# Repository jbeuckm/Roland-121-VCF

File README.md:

# Roland-121-VCF
Based on http://www.frequencycentral.co.uk/wp-content/uploads/2012/05/Roland-121-VCF-Build-Doc.pdf

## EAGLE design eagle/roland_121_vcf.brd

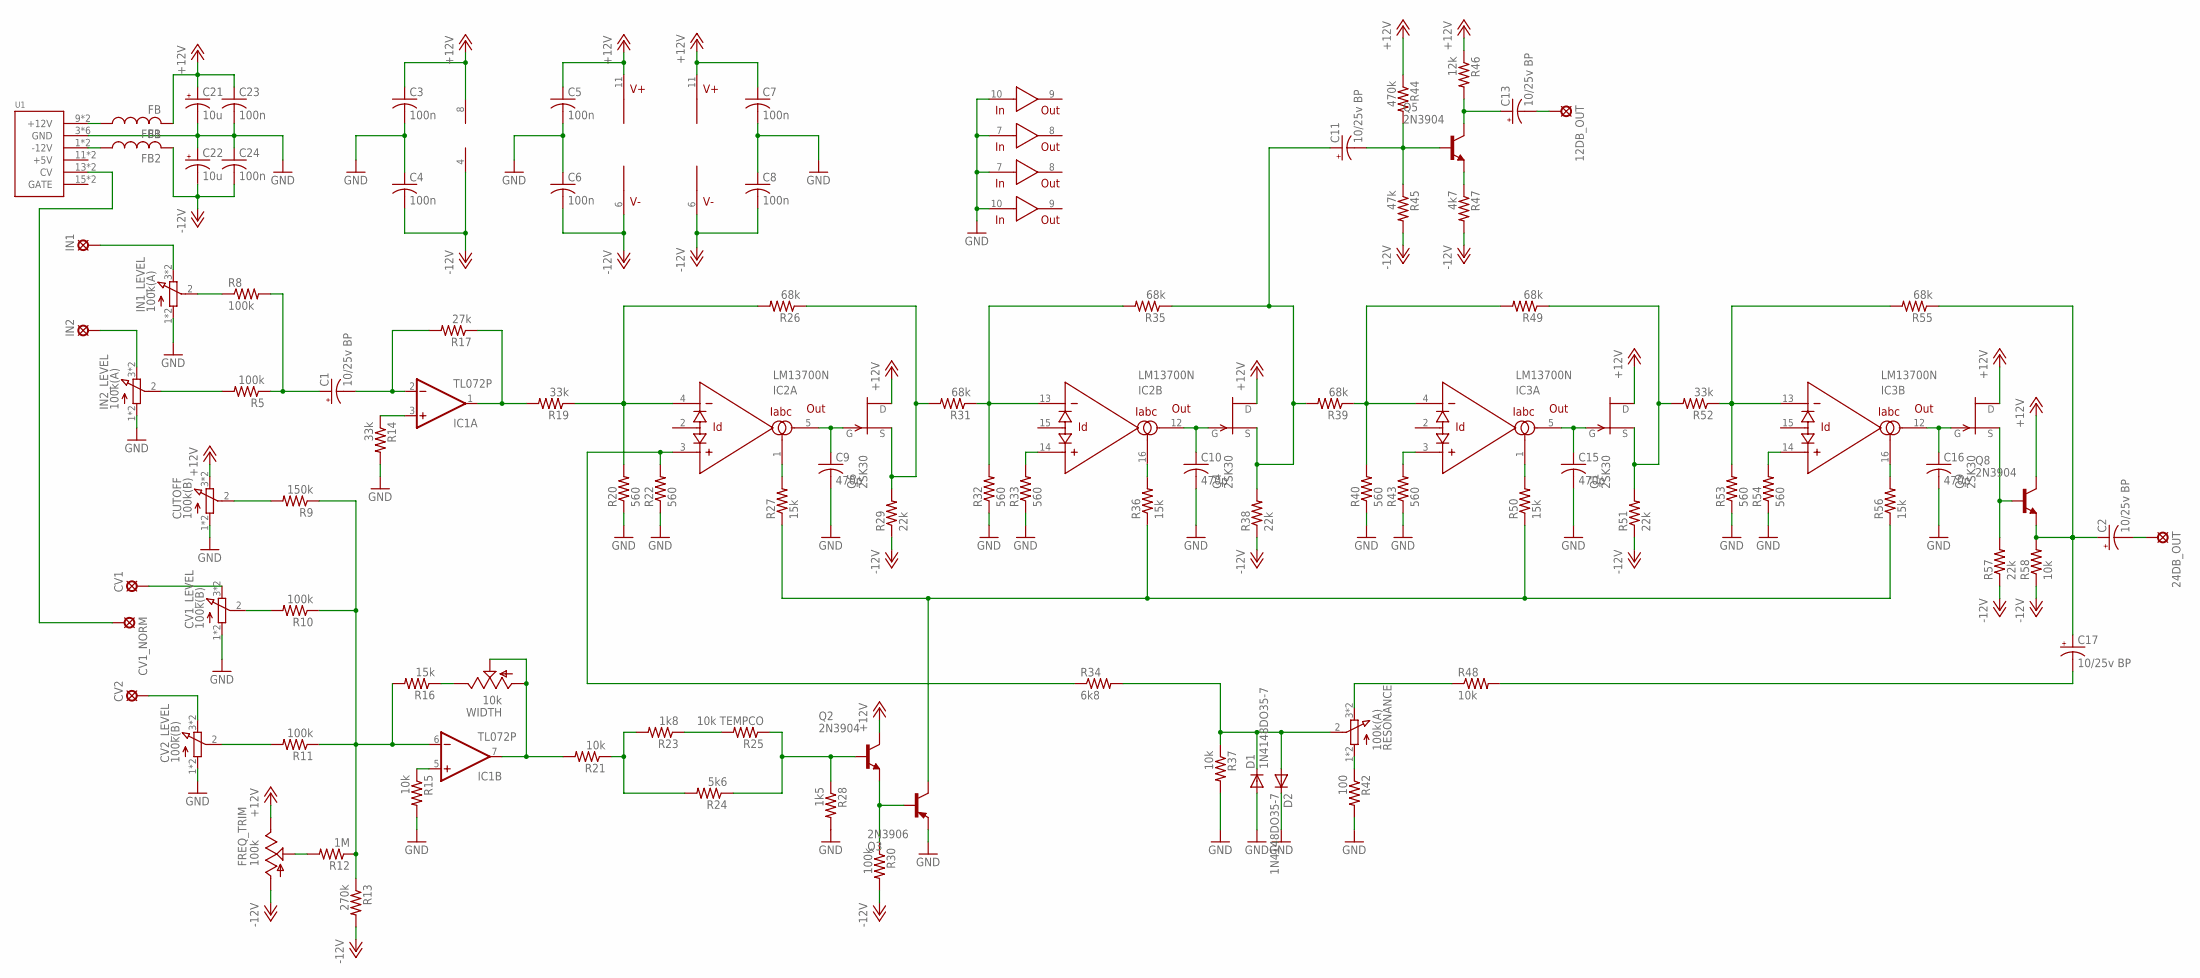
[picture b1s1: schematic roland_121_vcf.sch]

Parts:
12DB_OUT, 24DB_OUT: LSP10
C1, C2, C11, C13, C17: 10/25v BP; B45181A
C3, C4, C5, C6, C7, C8: 100n; C1206
C9, C10, C15, C16: 470p; C025-030X050
C21, C22: 10u; B45181A
C23, C24: 100n; C050-024X044
CUTOFF: 100k(B); 3RP/1610N
CV1, CV1_NORM, CV2: LSP10
CV1_LEVEL, CV2_LEVEL: 100k(B); 3RP/1610N
D1, D2: 1N4148DO35-7; DO35-7
FB1, FB2: FB
FREQ_TRIM: 100k; B64W
IC1: TL072P; DIL08
IC2, IC3: LM13700N; DIL16
IN1, IN2: LSP10
IN1_LEVEL, IN2_LEVEL: 100k(A); 3RP/1610N
Q1, Q4, Q6, Q9: 2SK30; TO92
Q2, Q5, Q8: 2N3904; TO92
Q3: 2N3906; TO92
R5, R8, R10, R11, R30: 100k; 0207/7
R9: 150k; 0207/7
R12: 1M; 0207/7
R13: 270k; 0207/7
R14, R19, R52: 33k; 0207/7
R15, R21, R37, R48, R58: 10k; 0207/7
R16, R27, R36, R50, R56: 15k; 0207/7
R17: 27k; 0207/7
R20, R22, R32, R33, R40, R43, R53, R54: 560; 0207/7
R23: 1k8; 0207/7
R24: 5k6; 0207/7
R25: 10k TEMPCO; 0207/7
R26, R31, R35, R39, R49, R55: 68k; 0207/7
R28: 1k5; 0207/7
R29, R38, R51, R57: 22k; 0207/7
R34: 6k8; 0207/7
R42: 100; 0207/7
R44: 470k; 0207/7
R45: 47k; 0207/7
R46: 12k; 0207/7
R47: 4k7; 0207/7
RESONANCE: 100k(A); 3RP/1610N
U1: POWER; POWER_16
WIDTH: 10k; B64W

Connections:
+12V: C3.1, C5.1, C7.1, C21.+, C23.1, CUTOFF.3 (E), CUTOFF.6 (E), FB1.P$2 (2), FREQ_TRIM.E, IC1.8 (V+), IC2.11 (V+), IC3.11 (V+), Q1.1 (D), Q2.1 (C), Q4.1 (D), Q6.1 (D), Q8.1 (C), Q9.1 (D), R44.1, R46.1
-12V: C4.2, C6.2, C8.2, C22.-, C24.2, FB2.P$2 (2), FREQ_TRIM.A, IC1.4 (V-), IC2.6 (V-), IC3.6 (V-), R13.2, R29.1, R30.2, R38.1, R45.2, R47.2, R51.1, R57.1, R58.1
GND: C3.2, C4.1, C5.2, C6.1, C7.2, C8.1, C9.2, C10.2, C15.2, C16.2, C21.-, C22.+, C23.2, C24.1, CUTOFF.1 (A), CUTOFF.4 (A), CV1_LEVEL.1 (A), CV1_LEVEL.4 (A), CV2_LEVEL.1 (A), CV2_LEVEL.4 (A), D1.A, D2.C, IC2.7 (IN), IC2.10 (IN), IC3.7 (IN), IC3.10 (IN), IN1_LEVEL.1 (A), IN1_LEVEL.4 (A), IN2_LEVEL.1 (A), IN2_LEVEL.4 (A), Q3.3 (E), R14.2, R15.2, R20.1, R22.1, R28.2, R32.1, R33.1, R37.2, R40.1, R42.2, R43.1, R53.1, R54.1, U1.3 (GND), U1.4 (GND), U1.5 (GND), U1.6 (GND), U1.7 (GND), U1.8 (GND)
unnamed: IC2.1 (IABC), R27.2
unnamed: IC2.16 (IABC), R36.2
unnamed: IC2.13 (-IN), R31.1, R32.2, R35.2
unnamed: IC2.14 (+IN), R33.2
unnamed: IN2_LEVEL.2 (S), R5.2
unnamed: C1.+, R5.1, R8.2
unnamed: C1.-, IC1.2 (-IN), R17.2
unnamed: IC1.1 (OUT), R17.1, R19.2
unnamed: R16.1, WIDTH.E
unnamed: CV2_LEVEL.2 (S), R11.2
unnamed: IC1.3 (+IN), R14.1
unnamed: IC1.5 (+IN), R15.1
unnamed: IC3.1 (IABC), R50.2
unnamed: IC3.4 (-IN), R39.1, R40.2, R49.2
unnamed: IC1.6 (-IN), R9.1, R10.1, R11.1, R12.1, R13.1, R16.2
unnamed: FREQ_TRIM.P$1 (S), FREQ_TRIM.S, R12.2
unnamed: R23.1, R25.2
unnamed: R21.1, R23.2, R24.2
unnamed: Q2.2 (B), R24.1, R25.1, R28.1
unnamed: Q2.3 (E), Q3.2 (B), R30.1
unnamed: IC2.4 (-IN), R19.1, R20.2, R26.2
unnamed: IC2.3 (+IN), R22.2, R34.1
unnamed: IC3.3 (+IN), R43.2
unnamed: IC3.16 (IABC), R56.2
unnamed: IC3.13 (-IN), R52.1, R53.2, R55.2
unnamed: IC3.14 (+IN), R54.2
unnamed: Q6.3 (S), R26.1, R29.2, R31.2
unnamed: 24DB_OUT.MP, C2.-
unnamed: 12DB_OUT.MP, C13.-
unnamed: Q5.3 (E), R47.1
unnamed: C13.+, Q5.1 (C), R46.2
unnamed: C11.-, Q5.2 (B), R44.2, R45.1
unnamed: IN2.MP, IN2_LEVEL.3 (E), IN2_LEVEL.6 (E)
unnamed: C11.+, Q4.3 (S), R35.1, R38.2, R39.2
unnamed: C2.+, C17.+, Q8.3 (E), R55.1, R58.2
unnamed: Q1.3 (S), R49.1, R51.2, R52.2
unnamed: IC1.7 (OUT), R21.2, WIDTH.A, WIDTH.P$1 (S), WIDTH.S
unnamed: C9.1, IC2.5 (OUT), Q6.2 (G)
unnamed: C10.1, IC2.12 (OUT), Q4.2 (G)
unnamed: C15.1, IC3.5 (OUT), Q1.2 (G)
unnamed: C16.1, IC3.12 (OUT), Q9.2 (G)
unnamed: Q3.1 (C), R27.1, R36.1, R50.1, R56.1
unnamed: Q8.2 (B), Q9.3 (S), R57.2
unnamed: R42.1, RESONANCE.1 (A), RESONANCE.4 (A)
unnamed: C17.-, R48.2
unnamed: R48.1, RESONANCE.3 (E), RESONANCE.6 (E)
unnamed: D1.C, D2.A, R34.2, R37.1, RESONANCE.2 (S)
unnamed: CV1_LEVEL.2 (S), R10.2
unnamed: CV2.MP, CV2_LEVEL.3 (E), CV2_LEVEL.6 (E)
unnamed: CV1_NORM.MP, U1.13 (CV), U1.14 (CV)
unnamed: CUTOFF.2 (S), R9.2
unnamed: IN1_LEVEL.2 (S), R8.1
unnamed: IN1.MP, IN1_LEVEL.3 (E), IN1_LEVEL.6 (E)
unnamed: CV1.MP, CV1_LEVEL.3 (E), CV1_LEVEL.6 (E)
unnamed: FB1.P$1 (1), U1.9 (+12V), U1.10 (+12V)
unnamed: FB2.P$1 (1), U1.1 (-12V), U1.2 (-12V)

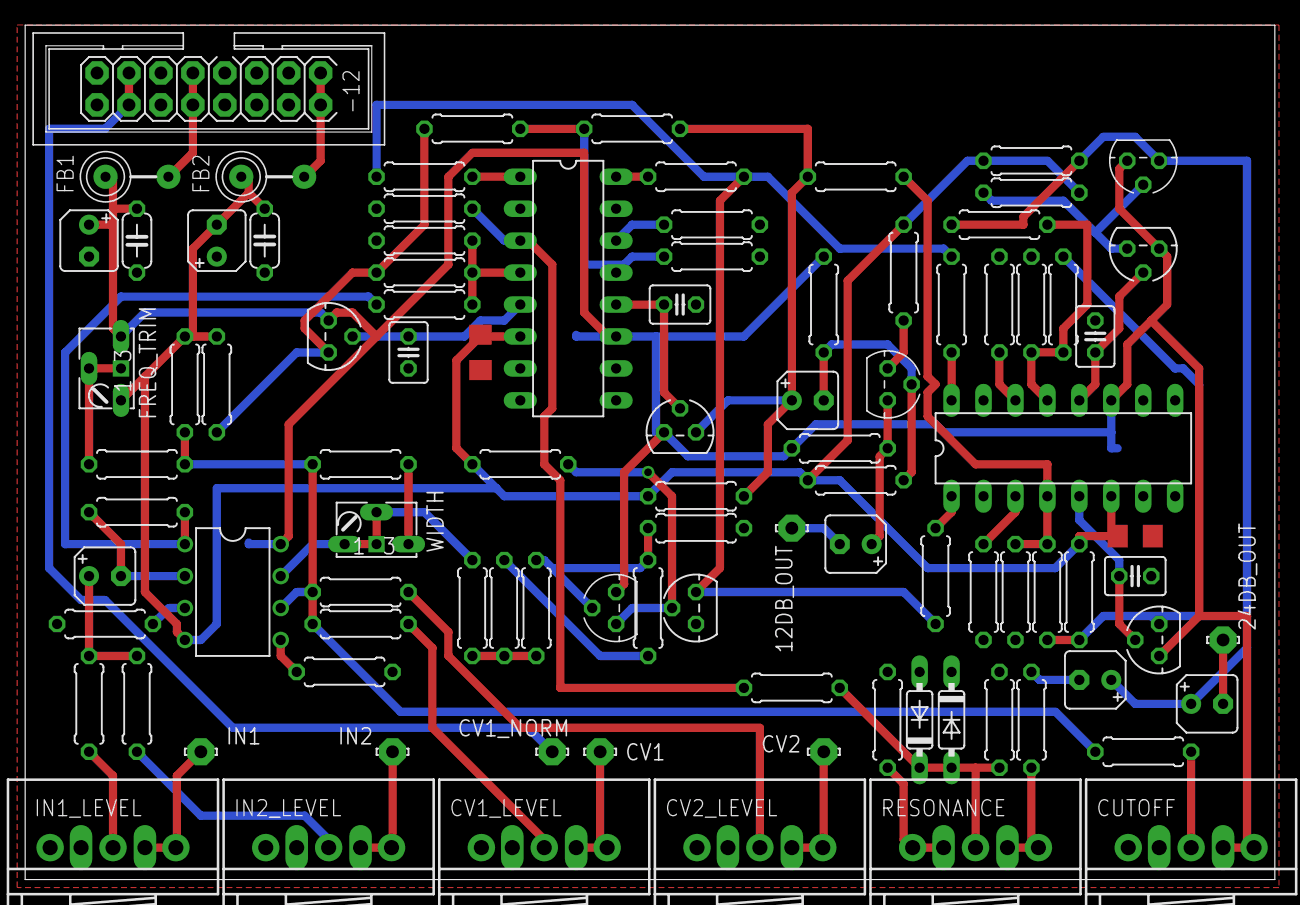
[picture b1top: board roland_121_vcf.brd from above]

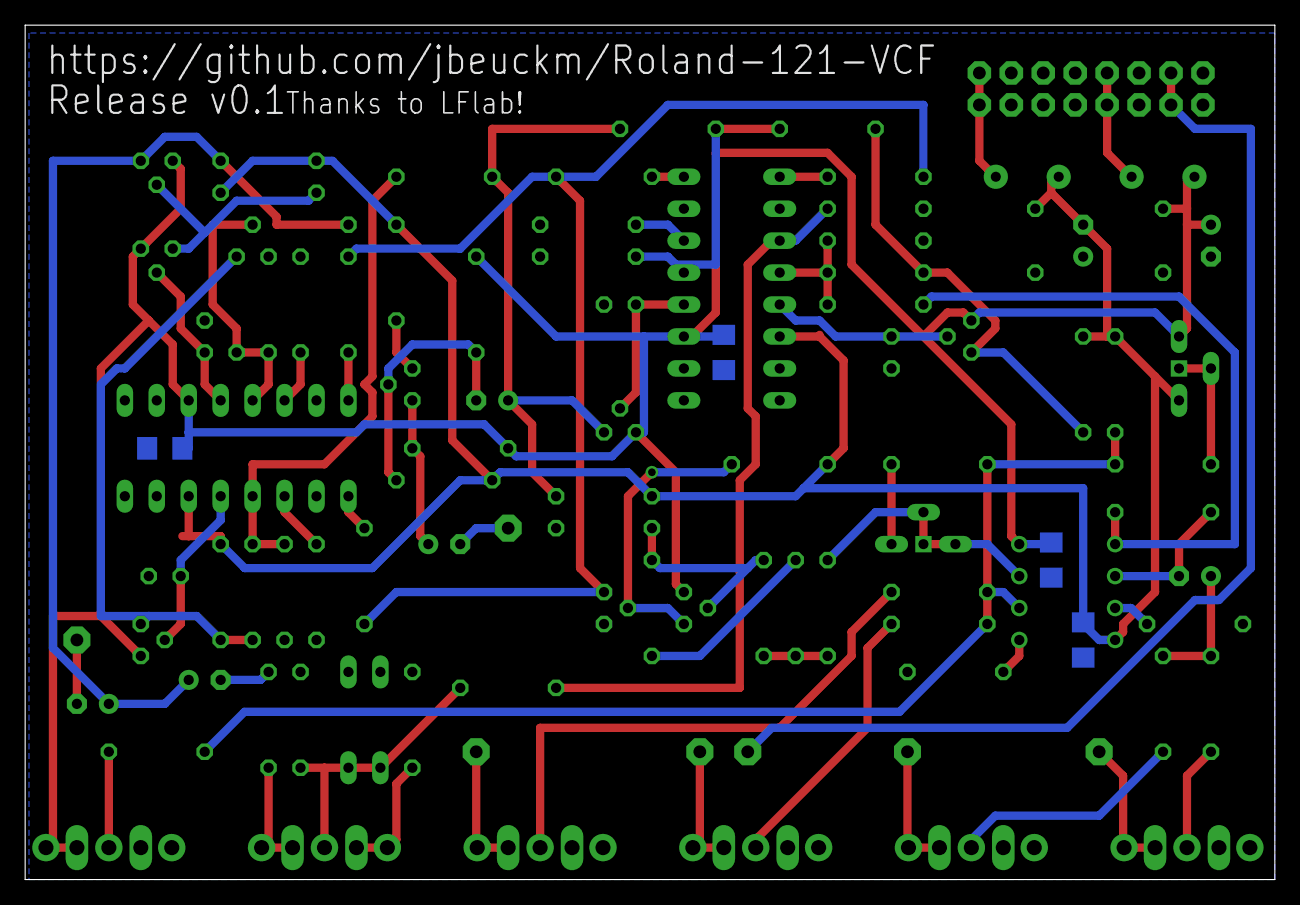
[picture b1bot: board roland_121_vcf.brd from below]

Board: 2 copper layers, 99.4 x 67.9 mm, 100 parts (4 on the bottom side), 59 nets.

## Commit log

2015-10-07 working on layout
2015-10-08 layout progress
2017-08-24 starting over with updated techniques
2017-08-24 layout begins
2017-08-24 parts on
2017-08-24 draft routed
2017-08-24 changed FET to 2sk30a
2017-08-25 ground planes
2017-08-26 cleaned up silkscreen
2017-08-27 smt decouplers, shrouded power, 16 or 9mm pots
2017-09-01 now with flexible trimmer pinout
2017-09-02 label tweaks
2017-09-22 layout image
2017-11-12 fixed the wrong valued resistor
2017-11-12 knob spacing
2017-11-12 panel try
2017-12-18 updated panel to 3mm
